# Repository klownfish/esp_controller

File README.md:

I guess you can see why i want a second revision

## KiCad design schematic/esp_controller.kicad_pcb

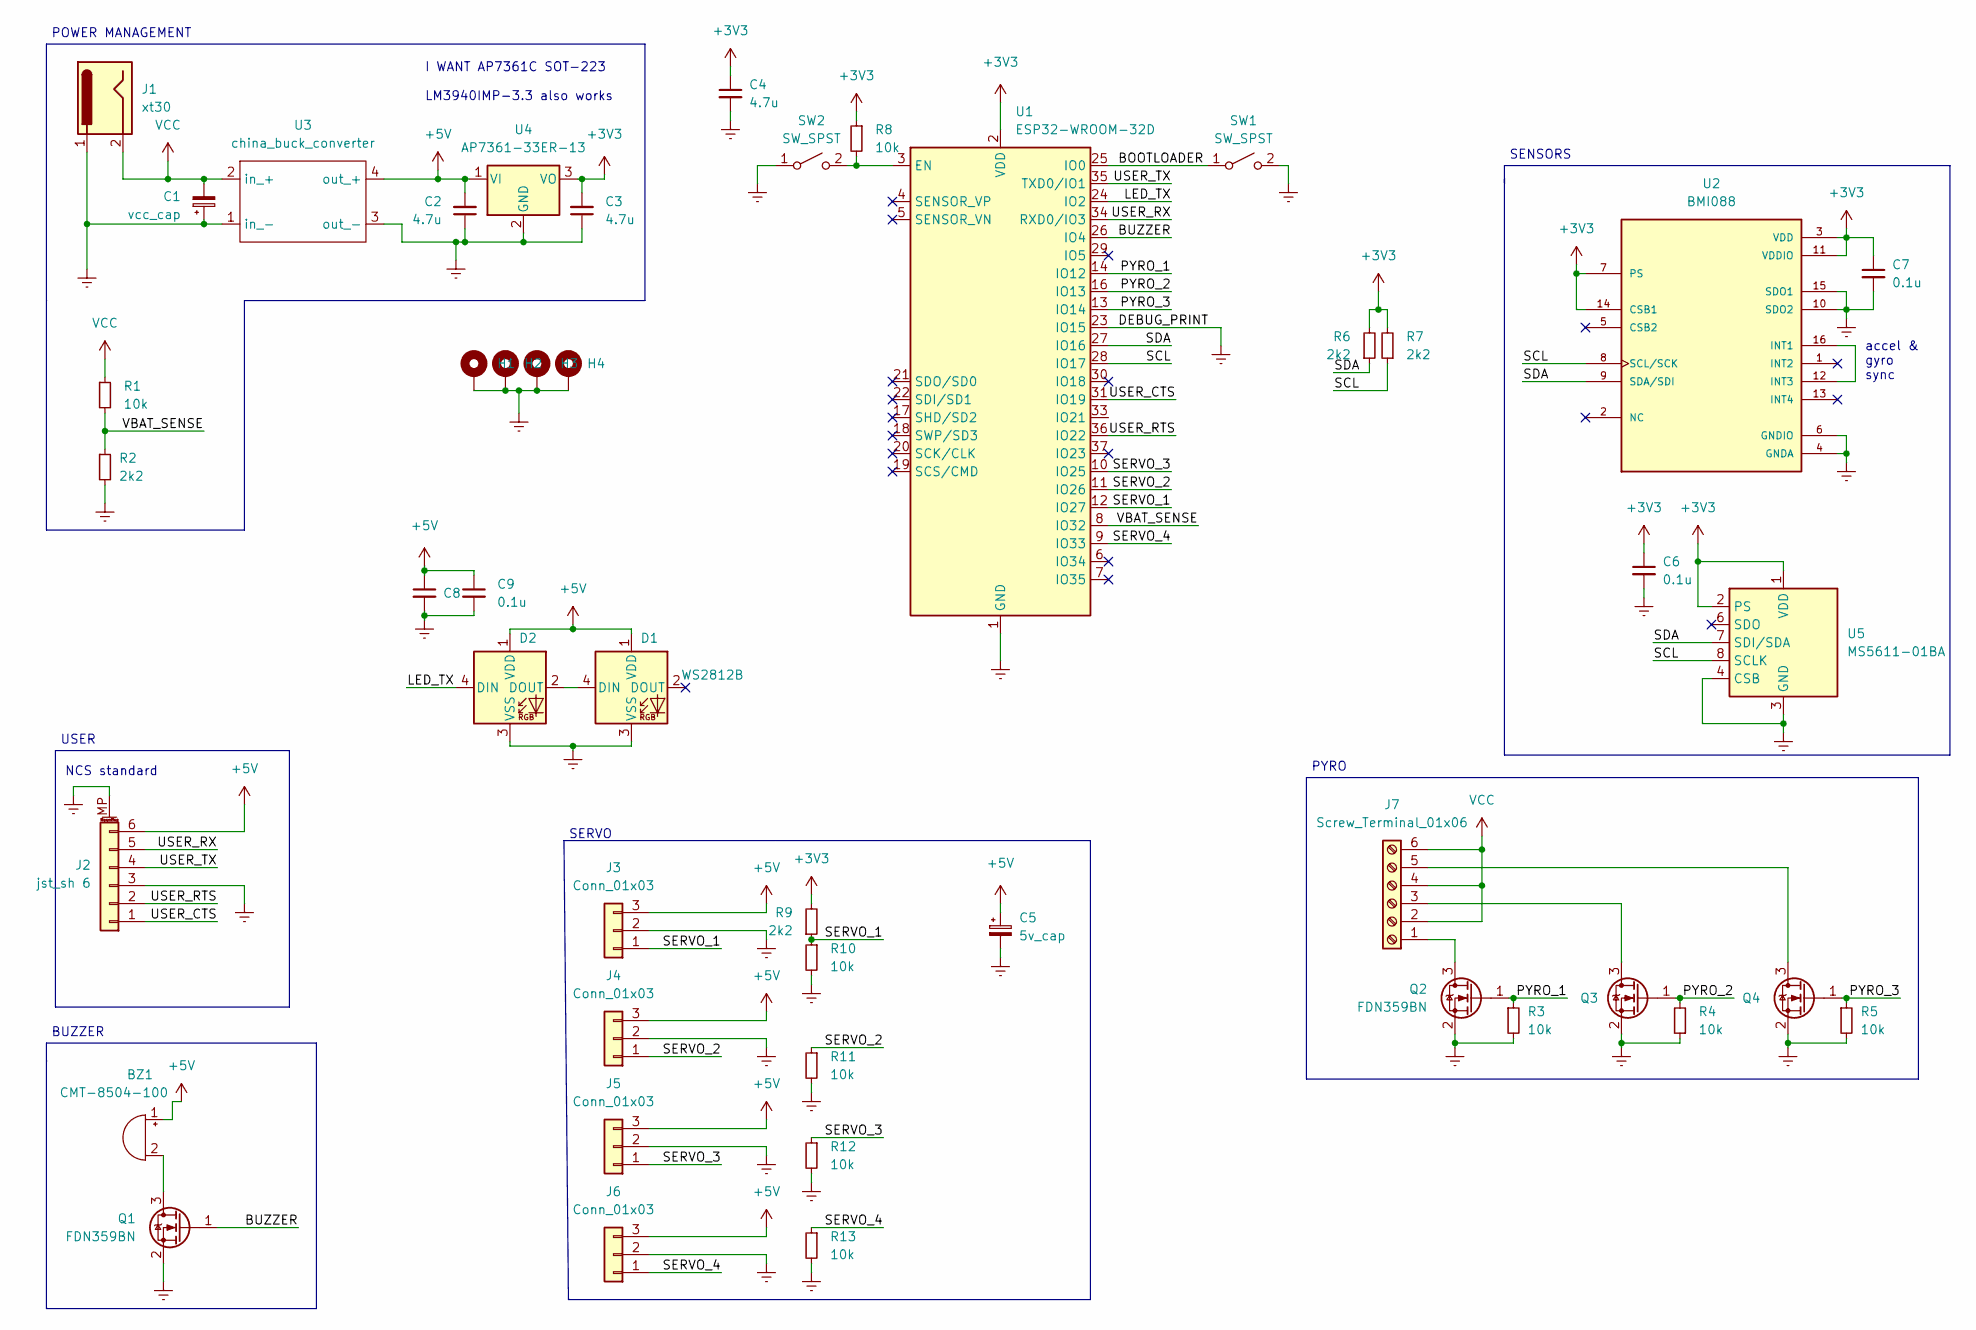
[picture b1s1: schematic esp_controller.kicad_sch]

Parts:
BZ1: CMT-8504-100; MagneticBuzzer_CUI_CMT-8504-100-SMT
C1: vcc_cap; CP_Radial_D5.0mm_P2.50mm
C2, C3, C4: 4.7u; C_0603_1608Metric
C5: 5v_cap; CP_Radial_D5.0mm_P2.50mm
C6, C7, C8, C9: 0.1u; C_0603_1608Metric
D1, D2: WS2812B; LED_WS2812B_PLCC4_5.0x5.0mm_P3.2mm
H1, H2, H3, H4: MountingHole_Pad; MountingHole_2.2mm_M2_Pad_Via
J1: xt30; AMASS_XT30PW-M_1x02_P2.50mm_Horizontal
J2: jst_sh 6; JST_SH_BM06B-SRSS-TB_1x06-1MP_P1.00mm_Vertical
J3, J4, J5, J6: Conn_01x03; PinHeader_1x03_P2.54mm_Vertical
J7: Screw_Terminal_01x06; TerminalBlock_TE_282834-6_1x06_P2.54mm_Horizontal
Q1, Q2, Q3, Q4: FDN359BN; SOT-23
R1, R3, R4, R5, R8, R10, R11, R12, R13: 10k; R_0603_1608Metric
R2, R6, R7, R9: 2k2; R_0603_1608Metric
SW1, SW2: SW_SPST; PinHeader_1x02_P1.27mm_Vertical
U1: ESP32-WROOM-32D; ESP32-WROOM-32
U2: BMI088; PQFN50P450X300X100-16N
U3: china_buck_converter; china_buck
U4: AP7361-33ER-13; SOT-223-3_TabPin2
U5: MS5611-01BA; LGA-8_3x5mm_P1.25mm

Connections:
+3V3: C3.2, C4.1, C6.1, C7.1, R6.2, R7.2, R8.1, R9.2, U1.2 (VDD), U2.3 (VDD), U2.7 (PS), U2.11 (VDDIO), U2.14 (CSB1), U4.3 (VO), U5.1 (VDD), U5.2 (PS)
+5V: BZ1.1 (-), C2.2, C5.1, C8.1, C9.1, D1.1 (VDD), D2.1 (VDD), J2.6, J3.3, J4.3, J5.3, J6.3, U3.4 (out_+), U4.1 (VI)
/BOOTLOADER: SW1.1 (A), U1.25 (IO0)
/BUZZER: Q1.1 (G), U1.26 (IO4)
/LED_TX: D2.4 (DIN), U1.24 (IO2)
/PYRO_1: Q2.1 (G), R3.1, U1.14 (IO12)
/PYRO_2: Q3.1 (G), R4.2, U1.16 (IO13)
/PYRO_3: Q4.1 (G), R5.1, U1.13 (IO14)
/SCL: R7.1, U1.28 (IO17), U2.8 (SCL/SCK), U5.8 (SCLK)
/SDA: R6.1, U1.27 (IO16), U2.9 (SDA/SDI), U5.7 (SDI/SDA)
/SERVO_1: J3.1, R9.1, R10.1, U1.12 (IO27)
/SERVO_2: J4.1, R11.1, U1.11 (IO26)
/SERVO_3: J5.1, R12.1, U1.10 (IO25)
/SERVO_4: J6.1, R13.1, U1.9 (IO33)
/USER_CTS: J2.1, U1.31 (IO19)
/USER_RTS: J2.2, U1.36 (IO22)
/USER_RX: J2.5, U1.34 (RXD0/IO3)
/USER_TX: J2.4, U1.35 (TXD0/IO1)
/VBAT_SENSE: R1.2, R2.1, U1.8 (IO32)
Earth: C1.1, C2.1, C3.1, C4.2, C5.2, C6.2, C7.2, C8.2, C9.2, D1.3 (VSS), D2.3 (VSS), H1.1, H2.1, H3.1, H4.1, J1.1, J2.3, J2.MP (MountPin), J3.2, J4.2, J5.2, J6.2, Q1.2 (S), Q2.2 (S), Q3.2 (S), Q4.2 (S), R2.2, R3.2, R4.1, R5.2, R10.2, R11.2, R12.2, R13.2, SW1.2 (B), SW2.1 (A), U1.1 (GND), U1.15 (GND), U1.23 (IO15), U1.38 (GND), U1.39 (GND), U2.4 (GNDA), U2.6 (GNDIO), U2.10 (SDO2), U2.15 (SDO1), U3.1 (in_-), U3.3 (out_-), U4.2 (GND), U5.3 (GND), U5.4 (CSB), U5.5 (CSB)
unnamed: BZ1.2 (+), Q1.3 (D)
unnamed: D1.4 (DIN), D2.2 (DOUT)
unnamed: J7.1, Q2.3 (D)
unnamed: J7.3, Q3.3 (D)
unnamed: J7.5, Q4.3 (D)
unnamed: R8.2, SW2.2 (B), U1.3 (EN)
unnamed: U2.12 (INT3), U2.16 (INT1)
VCC: C1.2, J1.2, J7.2, J7.4, J7.6, R1.1, U3.2 (in_+)

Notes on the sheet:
PYRO
USER
BUZZER
I WANT AP7361C SOT-223 LM3940IMP-3.3 also works
SERVO
NCS standard
accel & gyro sync
POWER MANAGEMENT
SENSORS

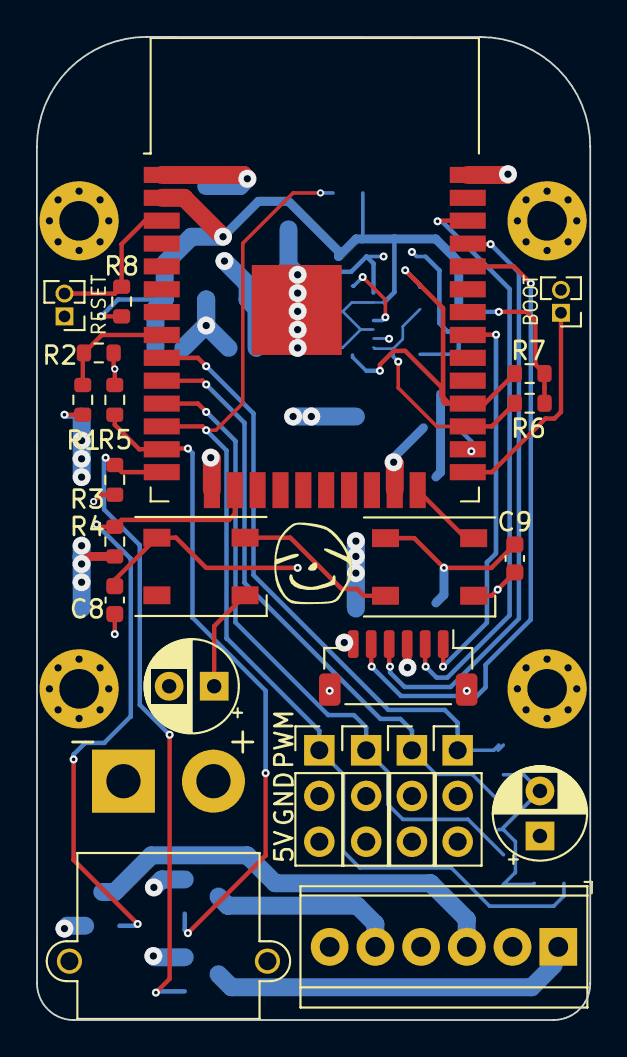
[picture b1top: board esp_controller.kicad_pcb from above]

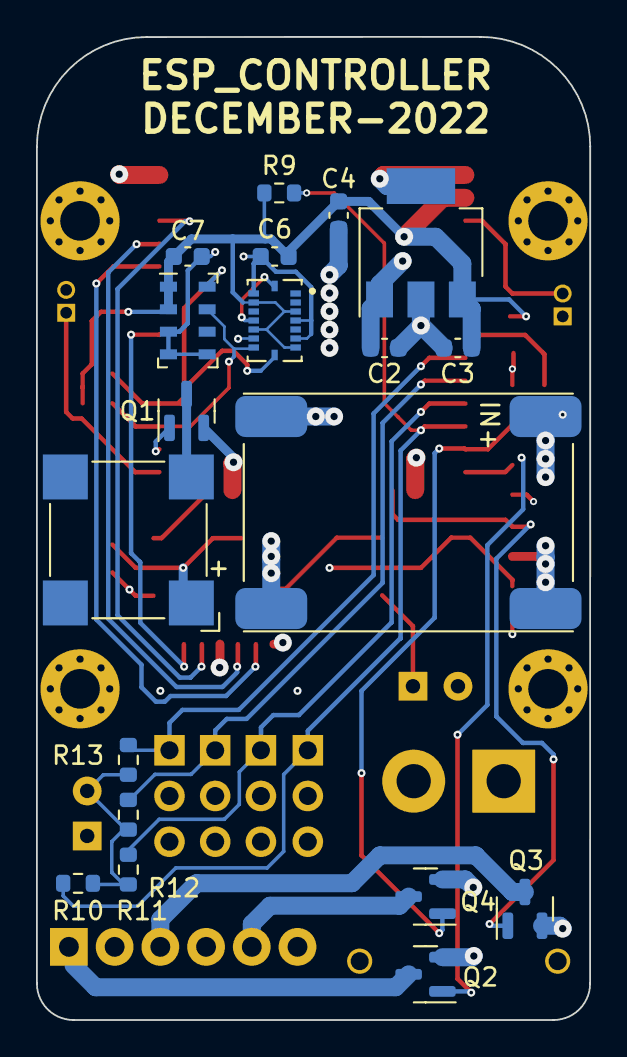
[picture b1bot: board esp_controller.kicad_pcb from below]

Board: 4 copper layers, 30.7 x 54.6 mm, 47 parts (19 on the bottom side), 28 nets.

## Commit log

2022-10-24 pcb second revision
2022-10-24 remove extra files
2022-10-24 proper markdown
2023-03-30 pre esp32 pico
